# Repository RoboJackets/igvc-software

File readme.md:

# RoboJackets IGVC 

Welcome to the RoboJackets IGVC software repo!
This document will give you a brief description of the repo's layout and an overview of the repo.
For more detailed information, check out the [github wiki](https://github.com/RoboJackets/igvc-software/wiki)
or the [RoboJackets wiki](wiki.robojackets.org).

<!-- The online API documentation generated by Doxygen is located [here](robojackets.github.io/igvc-software/). -->

## Folder Structure
The repo is comprised of multiple ROS packages and one sandbox folder for miscellaneous resources.
 * **igvc_description**
    *URDF files for our robot and gazebo meshes used for simulation*
 * **igvc_gazebo**
    *Helper nodes used for simulation purposes*
 * **igvc_msgs**
    *Custom ROS messages used in the various ROS packages*
 * **igvc_navigation**
    *Collection of nodes that form our navigation stack*
 * **igvc_perception**
    *Collection of nodes that form our perception stack, most notably the line detector*
 * **igvc_platform**
    *Nodes that are platform specific and used to communicate with the hardware, ie. IMU, joystick and motor controller*
 * **igvc_rviz_plugins**
    *RVIZ plugins that provide visualization for our stack.*
 * **igvc_utils**
    *A collection of utility nodes and classes*
 * **igvc_sandbox**
    *Miscellaneous resources, including the models used by the neural network, udev rules, and waypoints files*
 * **documents**
    *Research and design documents.*

## Building Code
 For an installation guide for ROS, check out the
 [installation guide on the RoboJackets wiki](https://wiki.robojackets.org/IGVC_Software_Installation_Instructions).

1. Clone the repository (with the git submodules) into the src directory of a catkin workspace:
    ```bash
    git clone https://github.com/RoboJackets/igvc-software --recursive
    ```

2. Install dependencies:
    ```bash
    cd igvc-software
    ./install_dependencies.sh
    ```

3. Use `catkin_make` in the workspace to build all the packages:
    ```bash
    catkin_make
    ```

4. Make sure the `devel/setup.bash` is sourced before using any of the nodes in this package:
    ```bash
   source devel/setup.bash
    ```

## Common Errors
- `Could not find a package configuration file provided by "parameter_assertions" with any of the following names:`
    - `parameter_assertions` comes from a git submodule. Initialize the submodules by doing
    `git submodule update --init --recursive`
- `Could not find a package configuration file provided by "XXXX" with any of the following names:"`
    - Make sure you have ran `rosdep install --from-paths src --ignore-src` in the `catkin_ws` folder already
    - If you still get this error after installing all dependencies, then that means that we forgot to include
    that package in our dependencies list.
    [File an issue](https://github.com/RoboJackets/igvc-software/issues) with the error message.

## Running Gazebo
You can get started with the IGVC code base right away by launching our simulator!

**Load up Swervi:**
The following command will load our platform into a simulated IGVC qualifications course:
```
roslaunch igvc_gazebo qualification.launch
```

**Navigate the course:**
After launching the gazebo simulation, launch the navigation stack for simulation:
```bash
roslaunch igvc_navigation navigation_simulation.launch
```

Alternatively, you can control the robot manually with a USB gamepad with this command:
```
roslaunch igvc_platform joystick_driver.launch
```

## Past Iterations
To view the software repository for our past differential drive robot, Jessiii, checkout the `jessiii-dev` branch.

## Contributing
Join the chat [here!](https://robojackets.slack.com/)

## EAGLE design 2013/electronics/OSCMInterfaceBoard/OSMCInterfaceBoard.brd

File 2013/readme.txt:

Take a deep breath. Welcome to IGVC 2013

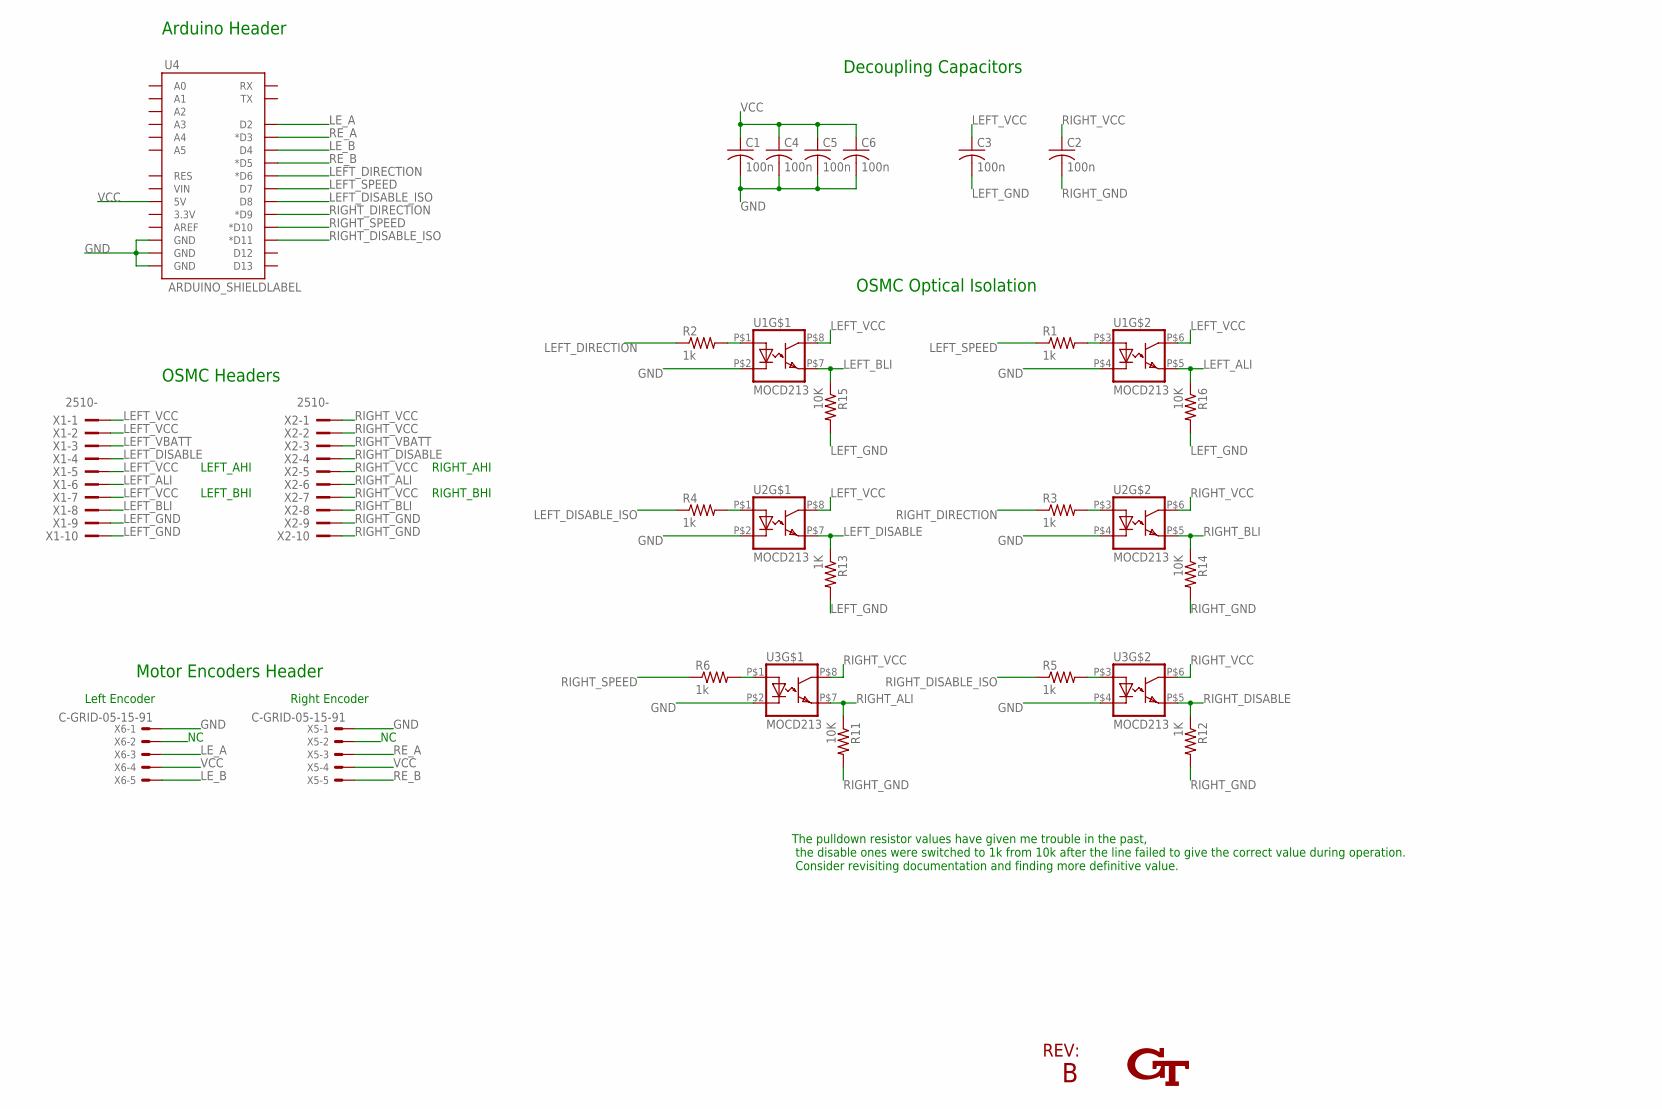
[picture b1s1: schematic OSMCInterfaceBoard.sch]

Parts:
C1, C2, C3, C4, C5, C6: 100n; C0603
GT1: INTERLOCKING_GTSTOP_.5_INCH; GT_STOP_.5INCH
R1, R2, R3, R4, R5, R6: 1k; R0603
R11, R14, R15, R16: 10K; R0603
R12, R13: 1K; R0603
U1, U2, U3: MOCD213; SOIC-8
U4: ARDUINO_SHIELDLABEL; DUEMILANOVE_SHIELD
U$1: B; REV_BLOCK_14PT
X1, X2: 2510-; PAK100/2500-10
X5, X6: C-GRID-05-15-91; 15-91-05

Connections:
GND: C1.2, C4.2, C5.2, C6.2, U1.P$2 (C), U1.P$4 (C), U2.P$2 (C), U2.P$4 (C), U3.P$2 (C), U3.P$4 (C), U4.GND@0 (GND), U4.GND@1 (GND), U4.GND@2 (GND), X5.1, X6.1
LEFT_ALI: R16.1, U1.P$5 (EMIT), X1.6
LEFT_BLI: R15.1, U1.P$7 (EMIT), X1.8
LEFT_DIRECTION: R2.1, U4.D6 (*D6)
LEFT_DISABLE: R13.1, U2.P$7 (EMIT), X1.4
LEFT_DISABLE_ISO: R4.1, U4.D8
LEFT_GND: C3.2, R13.2, R15.2, R16.2, X1.9, X1.10
LEFT_SPEED: R1.1, U4.D7
LEFT_VBATT: X1.3
LEFT_VCC: C3.1, U1.P$6 (COL), U1.P$8 (COL), U2.P$8 (COL), X1.1, X1.2, X1.5, X1.7
LE_A: U4.D2, X6.3
LE_B: U4.D4, X6.5
unnamed: R2.2, U1.P$1 (A)
unnamed: R3.2, U2.P$3 (A)
unnamed: R6.2, U3.P$1 (A)
unnamed: R4.2, U2.P$1 (A)
unnamed: R1.2, U1.P$3 (A)
unnamed: R5.2, U3.P$3 (A)
RE_A: U4.D3 (*D3), X5.3
RE_B: U4.D5 (*D5), X5.5
RIGHT_ALI: R11.1, U3.P$7 (EMIT), X2.6
RIGHT_BLI: R14.1, U2.P$5 (EMIT), X2.8
RIGHT_DIRECTION: R3.1, U4.D9 (*D9)
RIGHT_DISABLE: R12.1, U3.P$5 (EMIT), X2.4
RIGHT_DISABLE_ISO: R5.1, U4.D11 (*D11)
RIGHT_GND: C2.2, R11.2, R12.2, R14.2, X2.9, X2.10
RIGHT_SPEED: R6.1, U4.D10 (*D10)
RIGHT_VBATT: X2.3
RIGHT_VCC: C2.1, U2.P$6 (COL), U3.P$6 (COL), U3.P$8 (COL), X2.1, X2.2, X2.5, X2.7
VCC: C1.1, C4.1, C5.1, C6.1, U4.5V, X5.4, X6.4

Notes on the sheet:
Motor Encoders Header
LEFT_AHI
LEFT_BHI
RIGHT_AHI
RIGHT_BHI
OSMC Headers
OSMC Optical Isolation
Decoupling Capacitors
Left Encoder
Right Encoder
Arduino Header
The pulldown resistor values have given me trouble in the past, the disable ones were switched to 1k from 10k after the line failed to give the correct value during operation. Consider revisiting documentation and finding more definitive value.

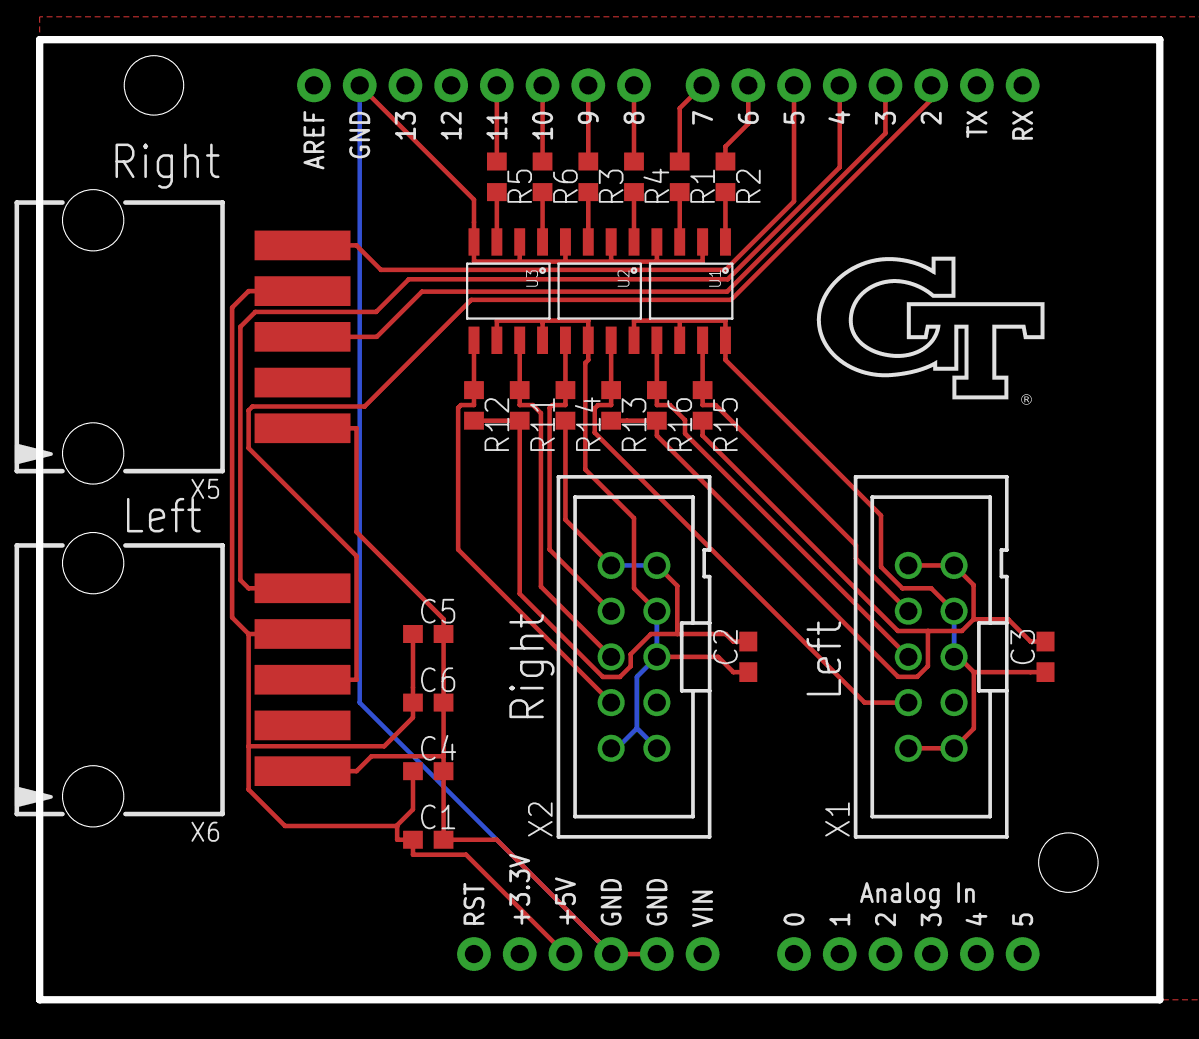
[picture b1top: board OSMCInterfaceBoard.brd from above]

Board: 2 copper layers, 62.2 x 53.3 mm, 28 parts (1 on the bottom side), 28 nets.

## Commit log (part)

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2020-12-31 Fix issues with gazebo world/model files
2020-12-31 Changed distutils to setuptools
2020-12-31 Updated elevation_mapping and fixed simulation launch files
2020-12-31 Added robot_localization_submodule
2020-12-31 Fix elevation_mapping submodule tracking
2020-12-31 Added updated version of nmea_navsat_driver
2020-12-31 Removed nmea_navsat_driver
2020-12-31 Removed unecessary spaces
2021-01-03 Refactor code and update data preparation pipelines
2021-01-03 Add new exception
2021-01-03 Refactor code
2021-01-04 Add a yaml config file
2021-01-04 Renamed folder and file
2021-01-04 Update Readme file
    Fixed a typo in the readme file.
2021-01-04 Add a working swervi submodule
2021-01-05 Add chassis, four swerve submodules, and lidar to swervi
2021-01-07 added a yaml file and refactored a ground filter.
2021-01-07 removed hard coded values in the util file.
2021-01-07 formated code using make format option.
2021-01-07 Feat/swerve sim (#819)
    * Added very basic peg and wheel model for swerve bot
    * Add a working swervi submodule
    * Add models for swervi wheel and chassis
    * Add chassis, four swerve submodules, and lidar to swervi
2021-01-09 added a print statement
2021-01-12 Remove respawn=true so that simulations run
2021-01-16 Add comments to all swervi properties
2021-01-17 added an option to train a model using google colab.
2021-01-17 updated build instruction
2021-01-30 removed version dependencies in the requirement.txt files.
2021-01-31 Finished refactoring the scan_to_pointcloud node
2021-02-07 Forced GPU and uncommented wait for transformation lines
2021-02-07 Final pep8 changes
2021-02-07 Refactors the scan_to_pointcloud node into a header and cpp file
2021-02-10 Added 'rosdep update' to install_dependencies.sh
2021-02-14 Updated submodules
2021-02-14 Removed 'rosdep update' from install_dependcies
2021-02-14 Fixed .gitmodules
2021-02-28 simulation running but gridmap abstract art :(
2021-03-25 Fixed igvc.rules for imus
2021-04-17 Changed frame_ids so can visualize odom in rviz. Added magnetometer readings into ekf_localization_node_params so initial orientation accounted for in robot_localization pose_ekf
2021-04-25 Back Circle Files
2021-05-23 Removed navsat_transform_node stuff and integrated raw gps and wheel odom measurements directly. Weird stuff happening with gps still.
2021-05-23 Updated back_circle code
2021-06-04 slam finally working!
    Realized that there was a problem with the hector gazebo plugin which was producing the wrong latitudes and longitudes in the simulation. The wrong behavior was that along the +X axis (East) latitude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
2021-06-04 removed navsat transform stuff from launch
2021-06-05 Fixed problem with navsat transform node
2021-06-05 Fixed issues with pointcloud transform
2021-06-05 Tuned the back circle and removed slashes before frames
2021-06-05 Added dependencies for slam to run
2021-06-05 Added gtsam and geographiclib installation commands
2021-06-20 Added documentation for binary segmentation
2021-06-20 rename binary segmentation documentation
2021-07-07 Carried over changes from vikram's old branch
2021-07-08 yep nvm im dumb
2021-07-16 Added apt-get update
2021-07-18 remove apt update
2021-07-20 removed redundancies
2021-07-23 modified gtsam install
2021-07-24 Fixed GPS waypoints
2021-07-28 remove main.cpp zombie
2021-08-01 Cleaned up things
2021-08-16 Fixed problems with wheel odom
    Added initial yaw orientation for wheel odometer and cleaned up includes in cpp and h files
2021-08-19 Cleaned up stuff
2021-09-02 forgot to reset wheel factor vals
2021-09-02 format
2021-09-02 proper wheel odom noise
2021-10-21 Binary Segmentation Model Documentation (#831)
    * Added documentation for binary segmentation
    * rename binary segmentation documentation
    * Update readme.md
    * Apply suggestions from code review
2021-11-18 update comment
2021-11-25 Conversion of scan_to_pointcloud to a C++ class
2021-11-26 forgot to run clang-format on the CMakeLists
2021-11-26 More autoformatting issues
2021-11-26 Testing clang
2021-11-29 Formatting update
2021-12-01 Revert "No idea why these weren't formatted"
    This reverts commit 0a3477ccd1431588d409994f2b208be5b204ccea.
2021-12-02 Refactored camera launch file
    Right renamed to left
2021-12-02 Work in progress for line detection
2021-12-02 separating main.cpp fixes #739
2021-12-05 making ground_truth to a node fixes #739
2021-12-05 Added "required" to igvc_control.launch. Tested by killing the igvc_control node and seeing the entire stack die. (#860)
2021-12-07 creates the ground_truth node class fixes #739
2021-12-18 ground truth node fixes #739
2021-12-19 Got controls on swervi to work
2021-12-19 Added new msg for swerve control
2021-12-21 Created swervi control node
2021-12-21 minor changes
2021-12-22 added new motor controller code
2021-12-23 cleaned up comments
2021-12-29 Partially finished implementation of unit testing
2022-01-02 added unit tests for swerve joystick driver
2022-01-02 ran formatting
2022-01-02 Simulated swerve modules and swerve module motor controller (#864)
    * Got controls on swervi to work
    * Added option to use swervi instead of jessi in existing launch files
    * Added new msg for swerve control
    * Added velocity_quad msg to cmake
    * Created swervi control node
    * formatted
2022-01-06 Initial attempt of swerve drive steering controller
    im kinda dumb but idk I feel like this kinda works. I'll give this another go tommorrow when I can actually think properly. also why are the buttons on my shirt placed super weird? Like the one at th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
2022-01-09 less dumb implementation that works lol
2022-01-09 minor change
2022-01-15 Fixed wheel shaking issue
    Added simple filter to mitigate spikes in derivative value and help mitigate against sensor noise.
2022-01-15 Added sensors to Swervi model (#863)
2022-01-16 Fixed directions for swerve drive and swervi
2022-01-16 Fixed issue with control
2022-01-16 Fixed faulty pointcloud test logic
2022-01-16 Improved the unit test design
2022-01-17 Scan To Pointcloud Node Rewrite (#871)
    * Conversion of scan_to_pointcloud to a C++ class
    * clang formatting
    * forgot to run clang-format on the CMakeLists
    * CMake autoformatting issue
    * More autoformatting issues
    * Testing clang
2022-01-17 Addressed PR comments
2022-01-20 suggested changes
2022-01-20 fixed issues with config
2022-01-20 corrected hector gps plugin for jessi and swervi
    Realized that there was a problem with the hector gazebo plugin which was producing the wrong latitudes and longitudes in the simulation. The wrong behavior was that along the +X axis (East) latitude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
2022-01-20 Fixed all waypoints that were wrong due to hector plugin bug
2022-01-21 Changed IMU heading defaults
    Typically most IMUs report 0 when facing north. Tried looking at the datasheet for the IMU we currently have (Hillcrest Labs FSM-9) but could not find that parameter. Probably will find it out during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
2022-01-22 initial attempt
2022-01-23 Split teb parameters into two files
2022-01-24 Fixed footprint in costmap_params
2022-01-27 Fixed nav_sim not using swerve drive
2022-01-27 most of the implementation
2022-01-30 publish fixes for segcam
2022-02-03 Design document for add noise simulation
2022-02-05 added node to igvc_platform makefile
2022-02-06 removed unneeded swervi files
2022-02-06 Removed Jessiii files
2022-02-06 checks and param cleanup
2022-02-10 fixed frame if for wheel odometer
2022-02-11 first seg_cam GTest not compiled yet
2022-02-17 debugging fixes
2022-02-19 fixed param issue with swerve_drive node
2022-02-19 fixed test
2022-02-19 removed unnecessary variables
2022-02-20 Feat/swerve wheel odometry (#880)
    * initial attempt
    * fixed frame if for wheel odometer
    * swerve odometry somewhat working
    * fixed issues with swerve wheel odom. accidentally transforming using yaw twice
    * fixed param issue with swerve_drive node
    * clean up unecessary code
2022-02-20 fixed bugs
2022-02-20 Fixed issues
2022-02-20 fixed naming errors
2022-02-24 Modified config. need to work on magnetometer
2022-02-27 Added example test for sim color detector
2022-02-27 updated navsat yaw offset to match updated simulated IMU yaw values
2022-02-27 adding back velocity pair so build passes
2022-02-27 minor localization changes
2022-02-27 added new corner tests, does not work currently
2022-02-28 syntax changes pt.2
2022-03-10 elevated swervi and tuned PID variables so swervi is able to go over ramps
2022-03-10 Configured robot_localization for 3D localization
2022-03-11 Revert "removed all jessi stuff"
    This reverts commit 94d8173d5855d7c2da872c15f676f28e821f02f2.
2022-03-11 Fixed unit tests
2022-03-13 removed unused method for segcam test
2022-03-14 removed another empty file
2022-03-16 removed extra code + comments, changed cmake structure
2022-03-17 removed unnecessary comments
2022-04-03 Add noise to simulation
2022-04-07 first pass
2022-04-10 third pass
2022-04-11 added test file for ground_truth
2022-04-11 last addition was a mistake
2022-04-11 Design/segmented camera info publisher (#882)
    * most of the implementation
    * publish fixes for segcam
    * updated vision.launch + fix incorrect include in cpp
    * added node to igvc_platform makefile
    * some typo fixes
    * fixed syntax, now compiles
2022-04-13 formatted and added back example plugins
2022-04-17 fixed all issues
2022-04-21 added back velocity pair bc its a pain otherwise
2022-04-22 Made minor fixes to refactored Sim Color Detector and modifed test class to test all 3 cameras.
2022-04-22 Removed extra spaces from test_sim_color_detector
2022-04-28 Igvc gazebo/ground truth (#884)
    * adding design document
    * Design document for add noise simulation
    * Add noise to simulation
    * add noise to simulation
    * add noise to simulation
    * made changes according to feedback
2022-05-04 made controller a PI controller which works so much better
2022-05-05 increased cost weight just to be safe
2022-05-06 able to test cameras and projections which is cool
2022-05-13 Tuned parameters so Swervi doesnt get stuck Added an inflation radius and increased the min obstacle distance so Swervi doesnt get stuck anymore. Also made the global inflation radius a bit less to a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
2022-05-13 updated center cam position
2022-05-20 preliminary work on making elevation mapping more complete
2022-05-23 reverting pid changes
2022-05-25 reconfigured files for physical testing
2022-05-27 added differential drive stuff
2022-05-28 added camera info to rosbag collection
2022-05-31 update files for colab training
2022-05-31 fixed existing jupyter notebook
2022-05-31 typo
2022-05-31 cleaned up multiclass segmentation node
2022-05-31 fixed build issues
2022-06-02 Added resizing functionality and main functions
2022-06-02 Added support for resizing images
2022-06-02 more pep8 fixes
2022-06-03 Feat/multiclass resize (#893)
    * Added resizing functionality and main functions
    * updated documentation
    * Added support for resizing images
    * Added a few examples
    * pep8 fixes
    * more pep8 fixes
2022-06-03 pep8?
2022-06-03 rosbag testing
2022-06-03 fixes topic paths and other testing fixes
2022-06-03 Multiclass Semantic Segmentation (#854)
    * Added changes from old multiclass segmentation branch
    * Final pep8 changes
    * Carried over changes from vikram's old branch
    * update comment
    * PEP8 newline fix
    * cleaned up multiclass segmentation node
2022-06-04 Drive encoders working on Swervi (#890)
    * drive encoders working on swervi
    * make format
2022-06-05 Multiclass Segmentation Binary Line Mask (#894)

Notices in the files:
parts and their libraries:
SparkFun-Boards: Licensing: CC v3.0 Share-Alike You are welcome to use this library for commercial purposes.
